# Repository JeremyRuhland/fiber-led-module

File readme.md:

## LED Control Module For Plastic Fiber ##

Push button control, RGB LED, coincell powered. Sleep mode for battery savings.

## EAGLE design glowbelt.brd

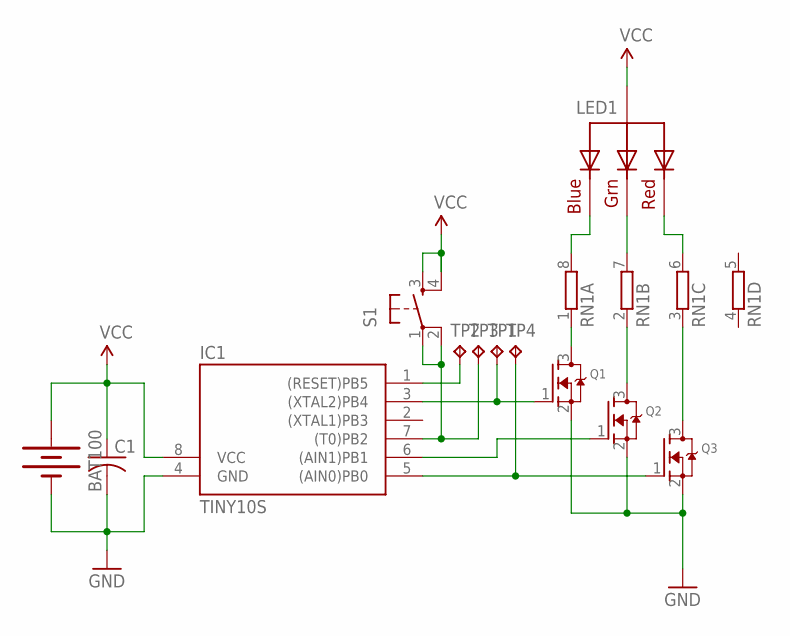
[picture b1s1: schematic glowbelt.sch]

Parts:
BAT100: BATTERY20SMD; BATTCON_20MM
C1: C-USC1206; C1206
IC1: TINY10S; SOIC8
LED1: RGBLED_CA-5MM; LED5MMRGB
Q1, Q2, Q3: MOSFET-NREFLOW; SOT23
RN1: 4R-NEXBS8V; EXBS8V
S1: TAC_SWITCHSMD; TACTILE_SWITCH_SMD
TP1, TP2, TP3, TP4: TPB1,27; B1,27

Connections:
GND: BAT100.2 (-), C1.2, IC1.4 (GND), Q1.2 (S), Q2.2 (S), Q3.2 (S)
MISO: IC1.3 ((XTAL2)PB4), Q1.1 (G), TP1.TP
MOSI: IC1.5 ((AIN0)PB0), Q3.1 (G), TP4.TP
unnamed: IC1.6 ((AIN1)PB1), Q2.1 (G)
unnamed: Q1.3 (D), RN1.1
unnamed: Q2.3 (D), RN1.2 (1)
unnamed: Q3.3 (D), RN1.3 (1)
unnamed: LED1.3 (GREEN), RN1.7 (2)
unnamed: LED1.4 (BLUE), RN1.8 (2)
unnamed: LED1.1 (RED), RN1.6 (2)
RST: IC1.1 ((RESET)PB5), TP2.TP
SCK: IC1.7 ((T0)PB2), S1.1, S1.2, TP3.TP
VCC: BAT100.1 (+), C1.1, IC1.8 (VCC), LED1.2 (VCC), S1.3, S1.4

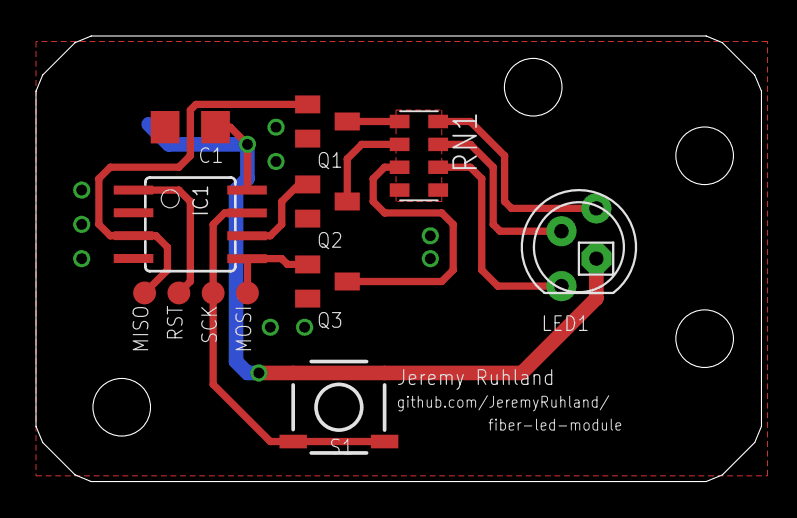
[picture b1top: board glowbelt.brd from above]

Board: 2 copper layers, 40.3 x 24.8 mm, 13 parts (1 on the bottom side), 13 nets.

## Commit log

2012-08-21 added optional current limiting resistor array
2012-08-23 upped isolation on both pours, updated image
2012-08-23 increased spacing for a couple vias

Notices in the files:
parts and their libraries:
sparkfun: Licensing: CC v3.0 Share-Alike You are welcome to use this library for commercial purposes.
